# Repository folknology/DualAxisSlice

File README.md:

DualAxisSlice
=============

Dual Axis Motion control Slice

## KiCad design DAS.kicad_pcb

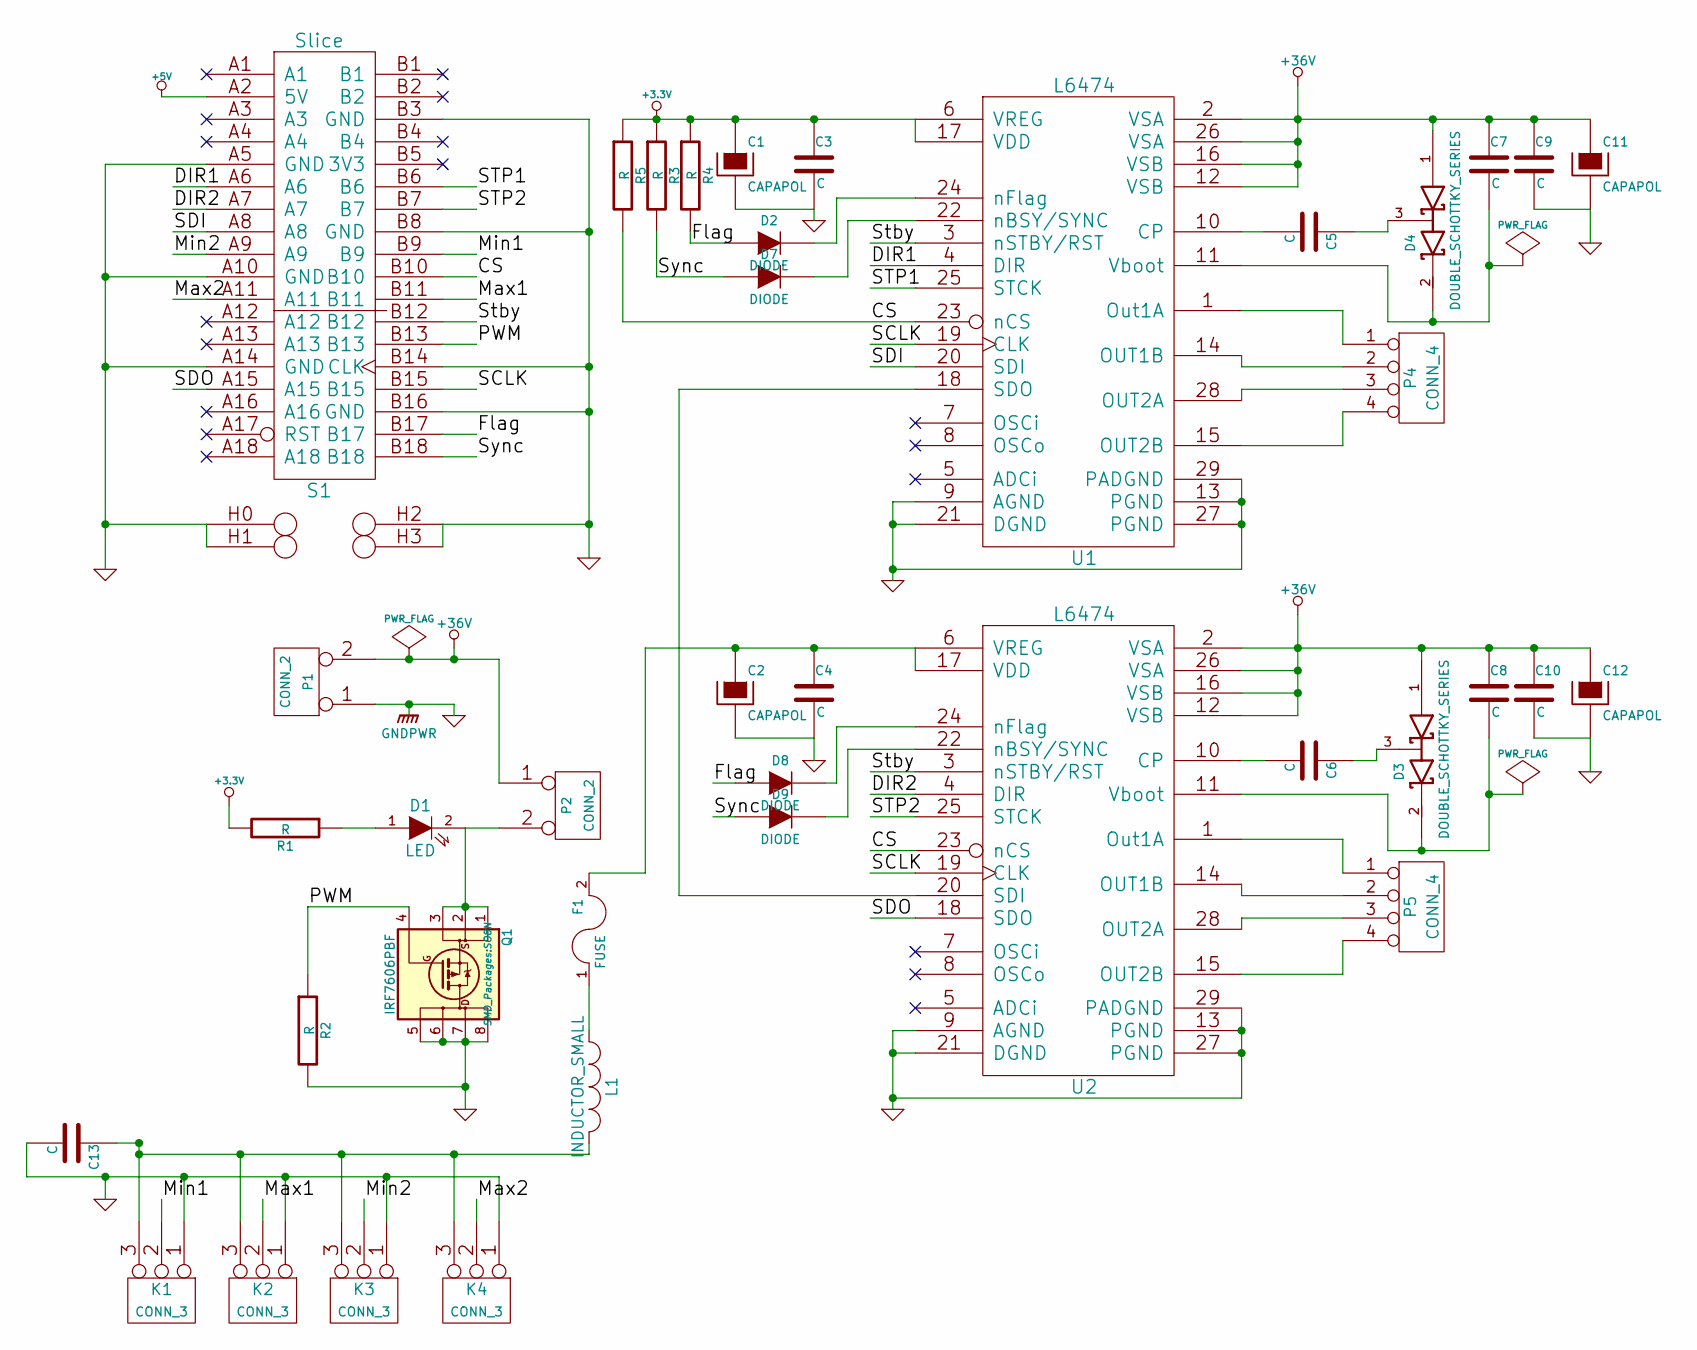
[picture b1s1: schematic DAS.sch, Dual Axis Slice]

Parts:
C1, C2: CAPAPOL; TantalC_SizeA_EIA-3216_Reflow
C3, C4, C5, C6, C7, C8, C9, C10, C13: C; c_0603
C11, C12: CAPAPOL; c_elec_5x5.8
D1: LED; LED-0805
D2, D7, D8, D9: DIODE; Diode-MiniMELF_Standard
D3, D4: DOUBLE_SCHOTTKY_SERIES; Diode_SOT23
F1: FUSE; Resistor_SMD1210_ReflowWave
K1, K2, K3, K4: CONN_3; SIL-3
L1: INDUCTOR_SMALL; Resistor_SMD1210_ReflowWave
P1: CONN_2; WAGO_734_2pin_Straight
P2: CONN_2; Pin_Header_Angled_1x02
P4, P5: CONN_4; Pin_Header_Angled_1x04
Q1: IRF7606PBF; SO8N
R1, R2, R3, R4, R5: R; Resistor_SMD0805_ReflowWave
S1: Slice; SLICE-Board
U1, U2: L6474; HTSSOP28

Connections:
+3.3V: C1.1, C3.1, R1.2, R3.1, R4.1, R5.1, U1.6 (VREG), U1.17 (VDD)
+5V: S1.A2 (5V)
+36V: C7.1, C8.1, C9.1, C10.1, C11.1, C12.1, D3.1 (Anode), D4.1 (Anode), P1.2 (PM), P2.1, U1.2 (VSA), U1.12 (VSB), U1.16 (VSB), U1.26 (VSA), U2.2 (VSA), U2.12 (VSB), U2.16 (VSB), U2.26 (VSA)
/CS: R5.2, S1.B10, U1.23 (nCS), U2.23 (nCS)
/DIR1: S1.A6, U1.4 (DIR)
/DIR2: S1.A7, U2.4 (DIR)
/Flag: D2.1 (A), D8.1 (A), R4.2, S1.B17
/Max1: K2.2 (PM), S1.B11
/Max2: K4.2 (PM), S1.A11
/Min1: K1.2 (PM), S1.B9
/Min2: K3.2 (PM), S1.A9
/PWM: Q1.4 (G), R2.1, S1.B13
/SCLK: S1.B15, U1.19 (CLK), U2.19 (CLK)
/SDI: S1.A8, U1.20 (SDI)
/SDO: S1.A15, U2.18 (SDO)
/STP1: S1.B6, U1.25 (STCK)
/STP2: S1.B7, U2.25 (STCK)
/Stby: S1.B12, U1.3 (nSTBY/RST), U2.3 (nSTBY/RST)
/Sync: D7.1 (A), D9.1 (A), R3.2, S1.B18
GNDPWR: C1.2, C2.2, C3.2, C4.2, C9.2, C10.2, C11.2, C12.2, C13.2, K1.1, K2.1, K3.1, K4.1, P1.1, Q1.5 (D), Q1.6 (D), Q1.7 (D), Q1.8 (D), R2.2, S1.A5 (GND), S1.A10 (GND), S1.A14 (GND), S1.B3 (GND), S1.B8 (GND), S1.B14 (CLK), S1.B16 (GND), S1.H0, S1.H1, S1.H2, S1.H3, U1.9 (AGND), U1.13 (PGND), U1.21 (DGND), U1.27 (PGND), U1.29 (PADGND), U2.9 (AGND), U2.13 (PGND), U2.21 (DGND), U2.27 (PGND), U2.29 (PADGND)
unnamed: C2.1, C4.1, F1.2, U2.6 (VREG), U2.17 (VDD)
unnamed: C5.1, D4.3 (AK)
unnamed: C5.2, U1.10 (CP)
unnamed: C6.1, D3.3 (AK)
unnamed: C6.2, U2.10 (CP)
unnamed: C7.2, D4.2 (cathode), U1.11 (Vboot)
unnamed: C8.2, D3.2 (cathode), U2.11 (Vboot)
unnamed: C13.1, K1.3, K2.3, K3.3, K4.3, L1.2
unnamed: D1.1 (A), R1.1
unnamed: D1.2 (K), P2.2 (PM), Q1.1 (S), Q1.2 (S), Q1.3 (S)
unnamed: D2.2 (K), U1.24 (nFlag)
unnamed: D7.2 (K), U1.22 (nBSY/SYNC)
unnamed: D8.2 (K), U2.24 (nFlag)
unnamed: D9.2 (K), U2.22 (nBSY/SYNC)
unnamed: F1.1, L1.1
unnamed: P4.1, U1.1 (Out1A)
unnamed: P4.2, U1.14 (OUT1B)
unnamed: P4.3, U1.28 (OUT2A)
unnamed: P4.4, U1.15 (OUT2B)
unnamed: P5.1, U2.1 (Out1A)
unnamed: P5.2, U2.14 (OUT1B)
unnamed: P5.3, U2.28 (OUT2A)
unnamed: P5.4, U2.15 (OUT2B)
unnamed: U1.18 (SDO), U2.20 (SDI)

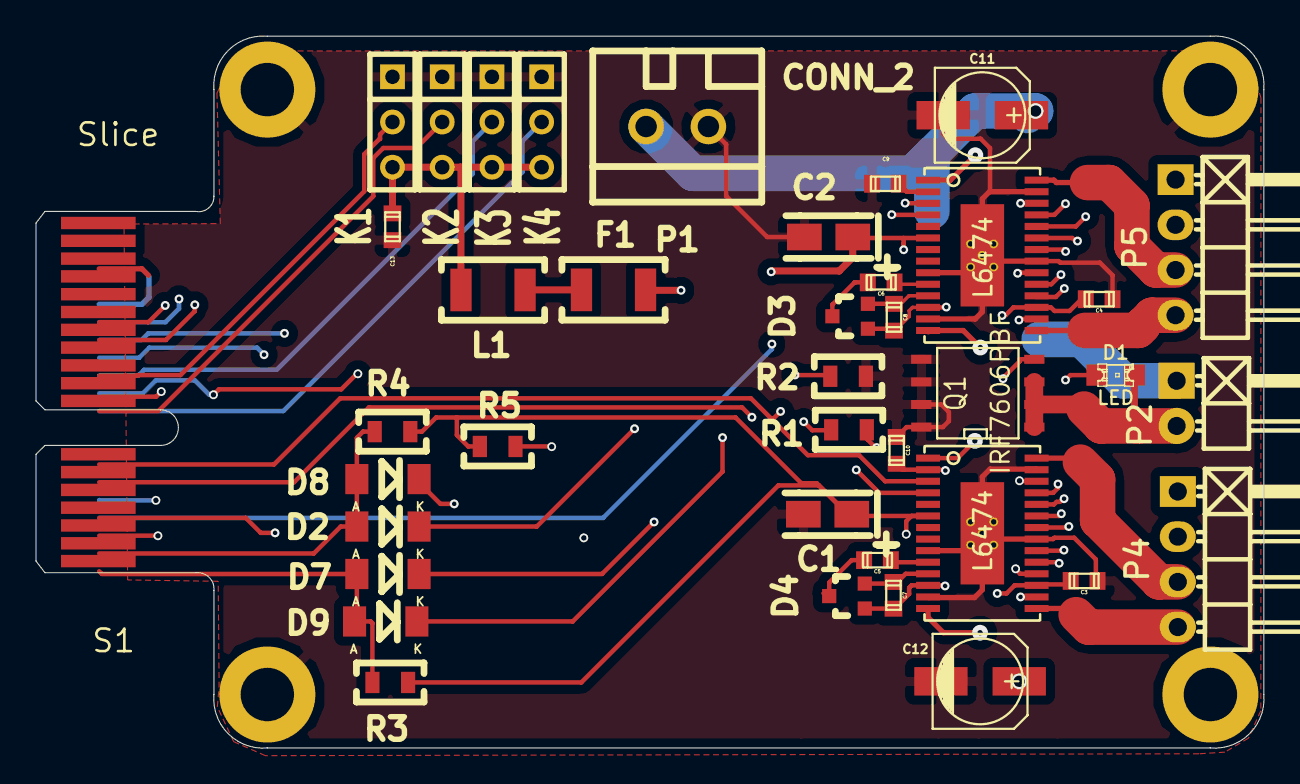
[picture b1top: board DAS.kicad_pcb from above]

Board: 4 copper layers, 69.0 x 40.0 mm, 39 parts (0 on the bottom side), 43 nets.

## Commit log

2014-08-02 Initial Github Commit
2014-08-02 Added Cern OH lisence
2014-08-02 Added schematic PDF
2014-08-02 Updated previews

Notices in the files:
DAS.sch:
Copyright Alan Wood 2014
